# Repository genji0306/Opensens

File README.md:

# Opensens
Opensource Potentiostat
Sau khi chia sẻ điện cực in SPE, Lab em đã nhận được sự nhiều sự quan tâm và liên hệ. Nhóm em nhận thấy là hiện tại việc nghiên cứu về Electrochemistry và Biosensor của các nhóm nghiên cứ ở trong VN còn nhiều khó khăn đặt biệt là về vấn đề thiết bị. Chính vì vậy, lab em quyết định chia sẻ phần nghiên cứu về thiết bị đo điện hoá Potentiostat/Galvanostat cho mọi người, hy vọng có thể giảm bớt khó khăn khi nghiên cứu trong nước Potentiostat/Galvanostat do nhóm DYNLAB- PGS. Thuỷ, thuộc Bộ Môn Điện Hoá, Đại Học Bách Khoa Hà Nội và nhóm PGS. Nguyên, ĐH KHTN HCM - phát triển – tên mã project là OEPS – tên chính thức là Opensens, được phát triển từ cuối năm 2017 với mục tiêu là tạo ra thiết bị đo điện hoá nhỏ gọn tin cậy độ phân giải cao, giá thành hợp lý để triển khai giám sát trên diện rộng. Version đầu tiên dựa trên phiên bản của TS. Dobbelaere và bản sau này của Irving (NCS của Dobbelaere). Phiên bản OEPS V1 dựa trên hardware với một số thay đổi về linh kiện, firmware và phần mềm. Sau 5 năm nghiên cứu, hiện nhóm đã phát triển nhiều Version khác nhau phục vụ cho nghiên cứu về Nguồn điện (Pin), Cảm Biến và giám sát môi trường. 
Trong link chia sẻ là bản OEPS V1/V2, MFO V1 và cả Software gốc/ Software của lab: 
- OEPS V1: Gồm một số tính năng: LSV, CV, CP, CA, Phóng nạp Pin - dải điện áp +-8V 30mA - hiệu chỉnh lỗi và tương thích software bản mới. (DAC 22 bits - độ phân giải 4pA) 
- OEPS V2: Dải điện áp +-12V 250mA - modify chống nhiễu, thay đổi linh kiện giá hợp lý hơn và chỉnh sửa lại Software.
- MFO V1: Phiên bản rút gọn đo 1 phép đo set up sẵn dùng cho y sinh/ môi trường. Có khả năng đo được hầu hết các phép đo LSV,CV,CP,CA, DPV, NPV, EIS(<34khz) (độ phân giải thấp – 12 bits) 
Các phiên bản trên đã được chạy thử nghiệm ít nhất 2 năm và nhiều nhất là từ khi dự án được tiến hành, đã so sánh với thiết bị thương mại như Autolab, Biologic và Palmsens. Các phiên bản khác của lab được tích hơn thêm Pulse technique và EIS sẽ sớm được opensource trong thời gian tiếp theo. Nếu muốn trải nghiệm thiết bị, xin mời mọi người qua DHBK HN ở Hà Nội gặp và Trường DH KHTN HCM ở HCM gặp PGS. Nguyên .

Chi phí linh kiện của thiết bị dao động từ $120-150, tuy nhiên thực tế tuỳ số lượng, đơn vị gia công và thuế nhập khẩu, chi phí sx rơi vào tầm 5-8tr/ thiết bị. Mọi người chỉ cần gửi link và liên hệ bên điện điện tử là được. Cũng chia sẻ luôn, tầm giữa tháng 4 tại bên lab sẽ đặt thêm linh kiện và gia công thiết bị (phiên bản mới) nhưng có chung nhiều linh kiện phiên bản cũ. Vì vậy nếu cần thì bên em có thể đặt giúp mọi người. Chi tiết xin liên hệ sdt: 033. 616.4867 

Ps: do phải tách repo Git để opensource nên dữ liệu sẽ được upload dần từ giờ tới cuối tuần

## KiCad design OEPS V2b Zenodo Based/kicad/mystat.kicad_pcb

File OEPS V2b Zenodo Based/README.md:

# mystat

A USB-controlled potentiostat/galvanostat for electrochemistry measurements.

## Introduction
This repository contains all the necessary design files to build a USB-controlled potentiostat/galvanostat.  This repository is a modification of the original [tdstatv3](https://github.com/thomasdob/tdstatv3) designed by Thomas Dobbelaere and described in detail at https://arxiv.org/pdf/1701.07650.pdf.  The purpose of this fork is to make design changes that facilitate placing the instrument inside a protected enclosure suitable for an electrochemical research environment, including a wet chemical lab bench, fume hood, or glove box.

This version of the hardware design uses a PCB with dimensions of 55.5 mm by 70 mm to fit an EMI-shielded [extruded aluminum case](https://www.hammfg.com/files/parts/pdf/1457C801E.pdf) (IP 54 rated).  This board will also fit a similar watertight [extruded aluminum case](https://www.hammfg.com/files/parts/pdf/1457C801.pdf) (IP 65 rated).  The terminal block and surface mounted USB mini-B connector in the original tdstav3 design by Thomas Dobbelaere were replaced with IP 67 rated circular connectors for the USB and electrode cables.

In order to fit the case, tall components (such as the reed relays and crystal) had to be moved from the board edges that slide into the slots in the extruded aluminum.  As a result, the entire PCB layout was changed.  All traces were made as wide as possible given the PCB size constraints and component footprints.  In addition, this forked design eliminates the power and mode LEDs present in the original tdstatv3.  The choice to eliminate LEDs was made to avoid the need for creating holes in the case that would accommodate them.

NOTE:  The design changes reported here have been implemented into physical hardware and tested to work.  However, there still may been unforseen problems with it.  I'm a Chemical Engineer with virtually zero experience in circuit design.  As such, I don't really know what I am doing, so you have been warned!

## Repository contents

### Directories
* `kicad`: KiCad design files (schematic diagram and PCB layout).
* `firmware`: Source code and compiled firmware for the PIC16F1459 microcontroller. Uses Microchip's XC8 compiler.
* `python`: Contains `tdstatv3.py`; run this file with Python 3 to bring up a GUI measurement tool.
* `gerber`: PCB design files in Gerber format, the universal standard for PCB manufacturing.
* `drivers`: Libusb drivers for Windows (not necessary on other operating systems).

### Files
* `full_schematic.pdf`: Complete schematic diagram in pdf format.
* `bom.csv`: Bill of materials for all PCB components.
* `partslist.csv`: Complete parts list, including enclosure, cables, and connectors, useful when ordering components.
* `pcb_3dview.png`: 3D rendering of the PCB design, useful for verification of the PCB layout.
* `pcb_fabrication_diagram.pdf`: Front side of PCB with component locations and values, useful for circuit assembly.
* `LICENSE`: a copy of the GNU GPLv3 license.
* `README.md`: This file.

## USB access on Linux
In order to access the device without requiring root privileges, create a file
`/etc/udev/rules.d/99-tdstatv3.rules` containing the line

```
SUBSYSTEM=="usb", ATTRS{idVendor}=="a0a0", ATTRS{idProduct}=="0002", GROUP="plugdev", MODE="0666"
```
This assumes that the current user is a member of the `plugdev` group, and that the default USB Vendor and Product ID's
as coded in the microcontroller firmware are used; if not, these values need to be adjusted.

## Credits
tdstatv3 created by:

* Thomas Dobbelaere
* email: thomas.dobbelaere@gmail.com

this fork created by:

* Matthew Yates
* email: myates@che.rochester.edu

## License
The contents of this repository are licensed under the GNU General Public License (GPL).

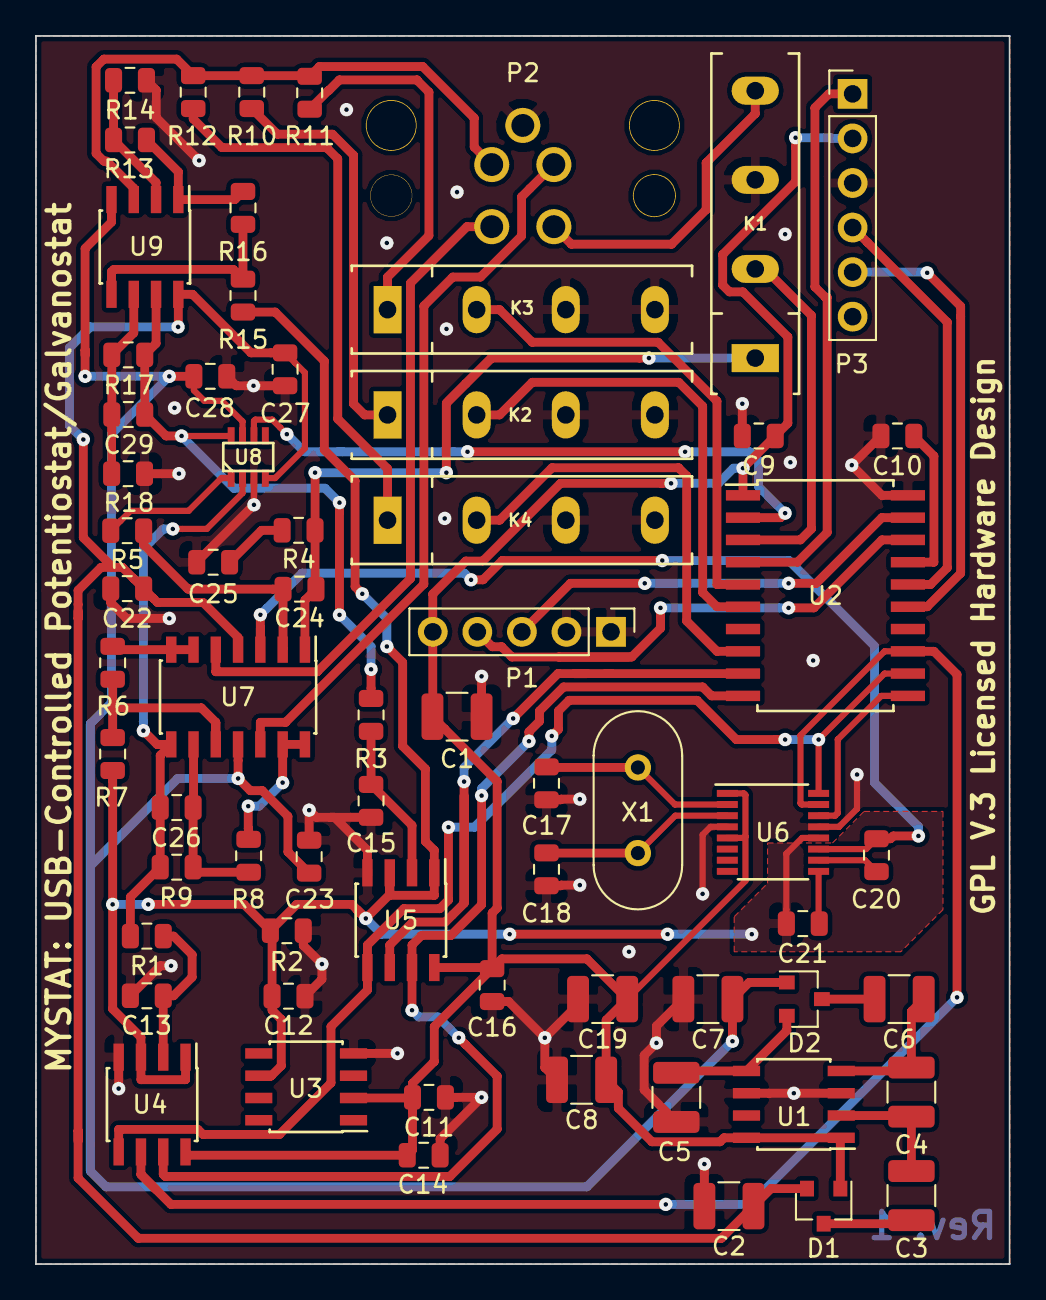
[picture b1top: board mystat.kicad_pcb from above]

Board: 2 copper layers, 55.5 x 70.0 mm, 66 parts (0 on the bottom side), 54 nets.

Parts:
C1, C2, C3, C4, C5, C6, C7, C8, C19: 10 µF; C_1210_3225Metric
C9, C10, C11, C12, C13, C14, C15, C16, C22, C23, C25, C27, C28: 0.1 µF; C_0805_2012Metric
C17, C18, C26, C29: 12 pF; C_0805_2012Metric
C20: 3.3 nF; C_0805_2012Metric
C21: 10 nF; C_0805_2012Metric
C24: 4700 pF; C_0805_2012Metric
D1, D2: BAT721S; SOT-23
K1, K2, K3, K4: 9007-05-01; RELAY-9007
P1: USB Terminal; PinHeader_1x05_P2.54mm_Vertical
P2: CELL; T4145035041-001
P3: ICSP; PinHeader_1x06_P2.54mm_Vertical
R1, R3: 1k; R_0805_2012Metric
R2, R5: 10k; R_0805_2012Metric
R4: 27R; R_0805_2012Metric
R6, R8: 240k*; R_0805_2012Metric
R7, R9, R15, R16, R17, R18: 75k*; R_0805_2012Metric
R10: 10R*; R_0805_2012Metric
R11: 1k*; R_0805_2012Metric
R12: 100k*; R_0805_2012Metric
R13: 18k*; R_0805_2012Metric
R14: 2k*; R_0805_2012Metric
U1: LM2662; SOIC-8_3.9x4.9mm_P1.27mm
U2: PIC16F1459; SOIC-20W_7.5x12.8mm_P1.27mm
U3: ADR421; SOIC-8_3.9x4.9mm_P1.27mm
U4, U5: MCP3553; SOIC-8_3.9x4.9mm_P1.27mm
U6: DAC1220; SSOP-16_3.9x4.9mm_P0.635mm
U7: OPA4192; SOIC-14_3.9x8.7mm_P1.27mm
U8: DG449; sot23-8
U9: OPA2192; SOIC-8_3.9x4.9mm_P1.27mm
X1: 2.5 MHz; Crystal_HC49-U_Vertical

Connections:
+5V: C1.1, C8.1, C9.1, C11.1, C14.1, C16.1, C19.1, D1.1, P1.1, P3.2, U1.1, U1.8, U2.1, U3.2, U4.8, U5.8, U6.1, U6.5
+9V: C2.1, C22.2, C27.2, D1.2, U7.4, U8.4, U9.8
-9V: C7.2, C23.1, C28.1, D2.1, U7.11, U8.7, U9.4
/CE: P2.3, R10.1, R11.1, R12.1, U9.3
/CELL_ON: K1.2, U2.3
/CS1: U2.11, U6.14
/CS2: U2.10, U4.7, U5.7
/ICSPCLK: P3.5, U2.15
/ICSPDAT: P3.4, U2.16
/I_MEAS: C29.2, R3.1, R17.2, U8.8, U9.7
/MCLR: P3.1, U2.4
/MODE_SW: U2.2, U8.6
/RANGE1: K2.2, U2.6
/RANGE2: K3.2, U2.5
/RANGE3: K4.2, U2.8
/RE: P2.4, U7.12
/SCK: U2.12, U4.5, U5.5, U6.16
/SDIO: U2.13, U4.6, U6.15
/SDIO2: U2.9, U5.6
/SE: P2.2, U7.5
/USB_D+: P1.3, U2.19
/USB_D-: P1.2, U2.18
/VREF: C12.1, C21.2, R2.1, R7.2, R15.1, U3.6, U4.1, U4.3, U5.1, U5.3, U6.12
/V_MEAS: C26.2, R1.1, R9.1, U7.8, U8.2
/WE: K1.4, P2.1
GND: C1.2, C2.2, C5.1, C7.1, C8.2, C9.2, C10.2, C11.2, C12.2, C13.2, C14.2, C15.2, C16.2, C17.2, C18.2, C19.2, C22.1, C23.2, C25.2, C27.1, C28.2, K1.3, K2.3, K2.4, K3.3, K3.4, K4.3, K4.4, P1.4, P1.5, P2.5, P3.3, R2.2, R14.2, R18.2, U1.3, U1.6, U2.20, U3.4, U4.4, U5.4, U6.4, U6.13, U8.3
unnamed: C3.1, D1.3
unnamed: C3.2, C4.1, U1.2
unnamed: C4.2, C6.1, U1.4
unnamed: C5.2, D2.2, U1.5
unnamed: C6.2, D2.3
unnamed: C10.1, U2.17
unnamed: C13.1, R1.2, U4.2
unnamed: C15.1, R3.2, U5.2
unnamed: C17.1, U6.2, X1.1
unnamed: C18.1, U6.3, X1.2
unnamed: C20.1, U6.10
unnamed: C20.2, U6.11, U7.3
unnamed: C21.1, U6.9
unnamed: C24.1, K1.1, R4.1, U7.1
unnamed: C24.2, R5.1, U7.2
unnamed: C25.1, R4.2
unnamed: C26.1, R8.1, R9.2, U7.9
unnamed: C29.1, R17.1, R18.1, U9.6
unnamed: K2.1, R10.2
unnamed: K3.1, R11.2
unnamed: K4.1, R12.2
unnamed: R5.2, U8.1
unnamed: R6.1, U7.6, U7.7
unnamed: R6.2, R7.1, U7.10
unnamed: R8.2, U7.13, U7.14
unnamed: R13.1, R14.1, U9.2
unnamed: R13.2, R16.1, U9.1
unnamed: R15.2, R16.2, U9.5

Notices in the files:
OEPS V2b Zenodo Based/kicad/mystat.kicad_pcb:
GPL v.3 Open Source Hardware Design
GPL V.3 Licensed Hardware Design
